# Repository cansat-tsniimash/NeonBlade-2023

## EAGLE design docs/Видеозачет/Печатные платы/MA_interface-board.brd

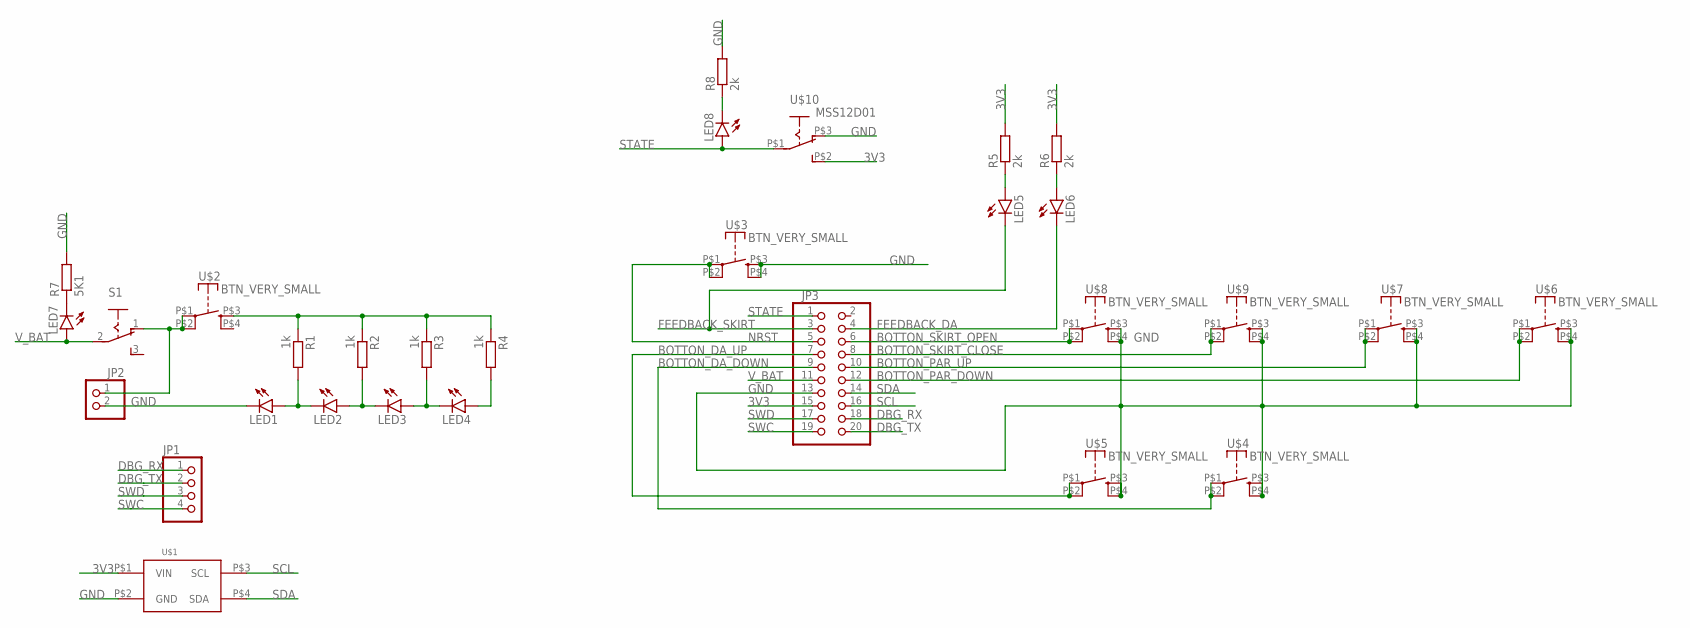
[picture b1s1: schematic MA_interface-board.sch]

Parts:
JP1: PINHD-1X4; 1X04
JP2: PINHD-1X2; 1X02
JP3: PINHD-2X10; 2X10
LED1, LED2, LED3, LED4, LED5, LED6, LED7, LED8: LEDSML0603; SML0603
R1, R2, R3, R4: 1k; R0603
R5, R6, R8: 2k; R0603
R7: 5K1; R0603
S1: UNICS-SWITCH
U$1: BME280BME280-PINS-ONLY; BME280-PINS-ONLY
U$2, U$3, U$4, U$5, U$6, U$7, U$8, U$9: BTN_VERY_SMALL
U$10: MSS12D01

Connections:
3V3: JP3.15, R5.2, R6.2, U$1.P$1 (VIN), U$10.P$2 (S)
BOTTON_DA_DOWN: JP3.9, U$4.P$1, U$4.P$2
BOTTON_DA_UP: JP3.7, U$5.P$1, U$5.P$2
BOTTON_PAR_DOWN: JP3.12, U$6.P$1, U$6.P$2
BOTTON_PAR_UP: JP3.10, U$7.P$1, U$7.P$2
BOTTON_SKIRT_CLOSE: JP3.8, U$9.P$1, U$9.P$2
BOTTON_SKIRT_OPEN: JP3.6, U$8.P$1, U$8.P$2
DBG_RX: JP1.1, JP3.18
DBG_TX: JP1.2, JP3.20
FEEDBACK_DA: JP3.4, LED6.C
FEEDBACK_SKIRT: JP3.3, LED5.C
GND: JP2.2, JP3.13, LED1.C, R7.2, R8.2, U$1.P$2 (GND), U$3.P$3 (S), U$3.P$4 (S), U$4.P$3 (S), U$4.P$4 (S), U$5.P$3 (S), U$5.P$4 (S), U$6.P$3 (S), U$6.P$4 (S), U$7.P$3 (S), U$7.P$4 (S), U$8.P$3 (S), U$8.P$4 (S), U$9.P$3 (S), U$9.P$4 (S), U$10.P$3 (O)
unnamed: LED1.A, LED2.C, R1.2
unnamed: LED2.A, LED3.C, R2.2
unnamed: LED3.A, LED4.C, R3.2
unnamed: LED4.A, R4.2
unnamed: LED7.C, R7.1
unnamed: JP2.1, S1.1 (O), U$2.P$1, U$2.P$2
unnamed: R1.1, R2.1, R3.1, R4.1, U$2.P$3 (S)
unnamed: LED5.A, R5.1
unnamed: LED6.A, R6.1
unnamed: LED8.C, R8.1
NRST: JP3.5, U$3.P$1, U$3.P$2
SCL: JP3.16, U$1.P$3 (SCL)
SDA: JP3.14, U$1.P$4 (SDA)
STATE: JP3.1, LED8.A, U$10.P$1
SWC: JP1.4, JP3.19
SWD: JP1.3, JP3.17
V_BAT: JP3.11, LED7.A, S1.2

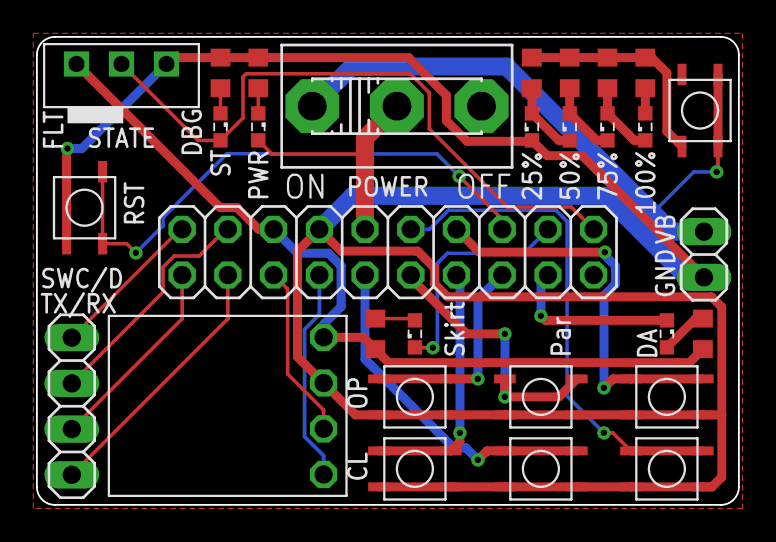
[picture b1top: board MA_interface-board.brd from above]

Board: 2 copper layers, 39.0 x 26.0 mm, 30 parts (0 on the bottom side), 29 nets.

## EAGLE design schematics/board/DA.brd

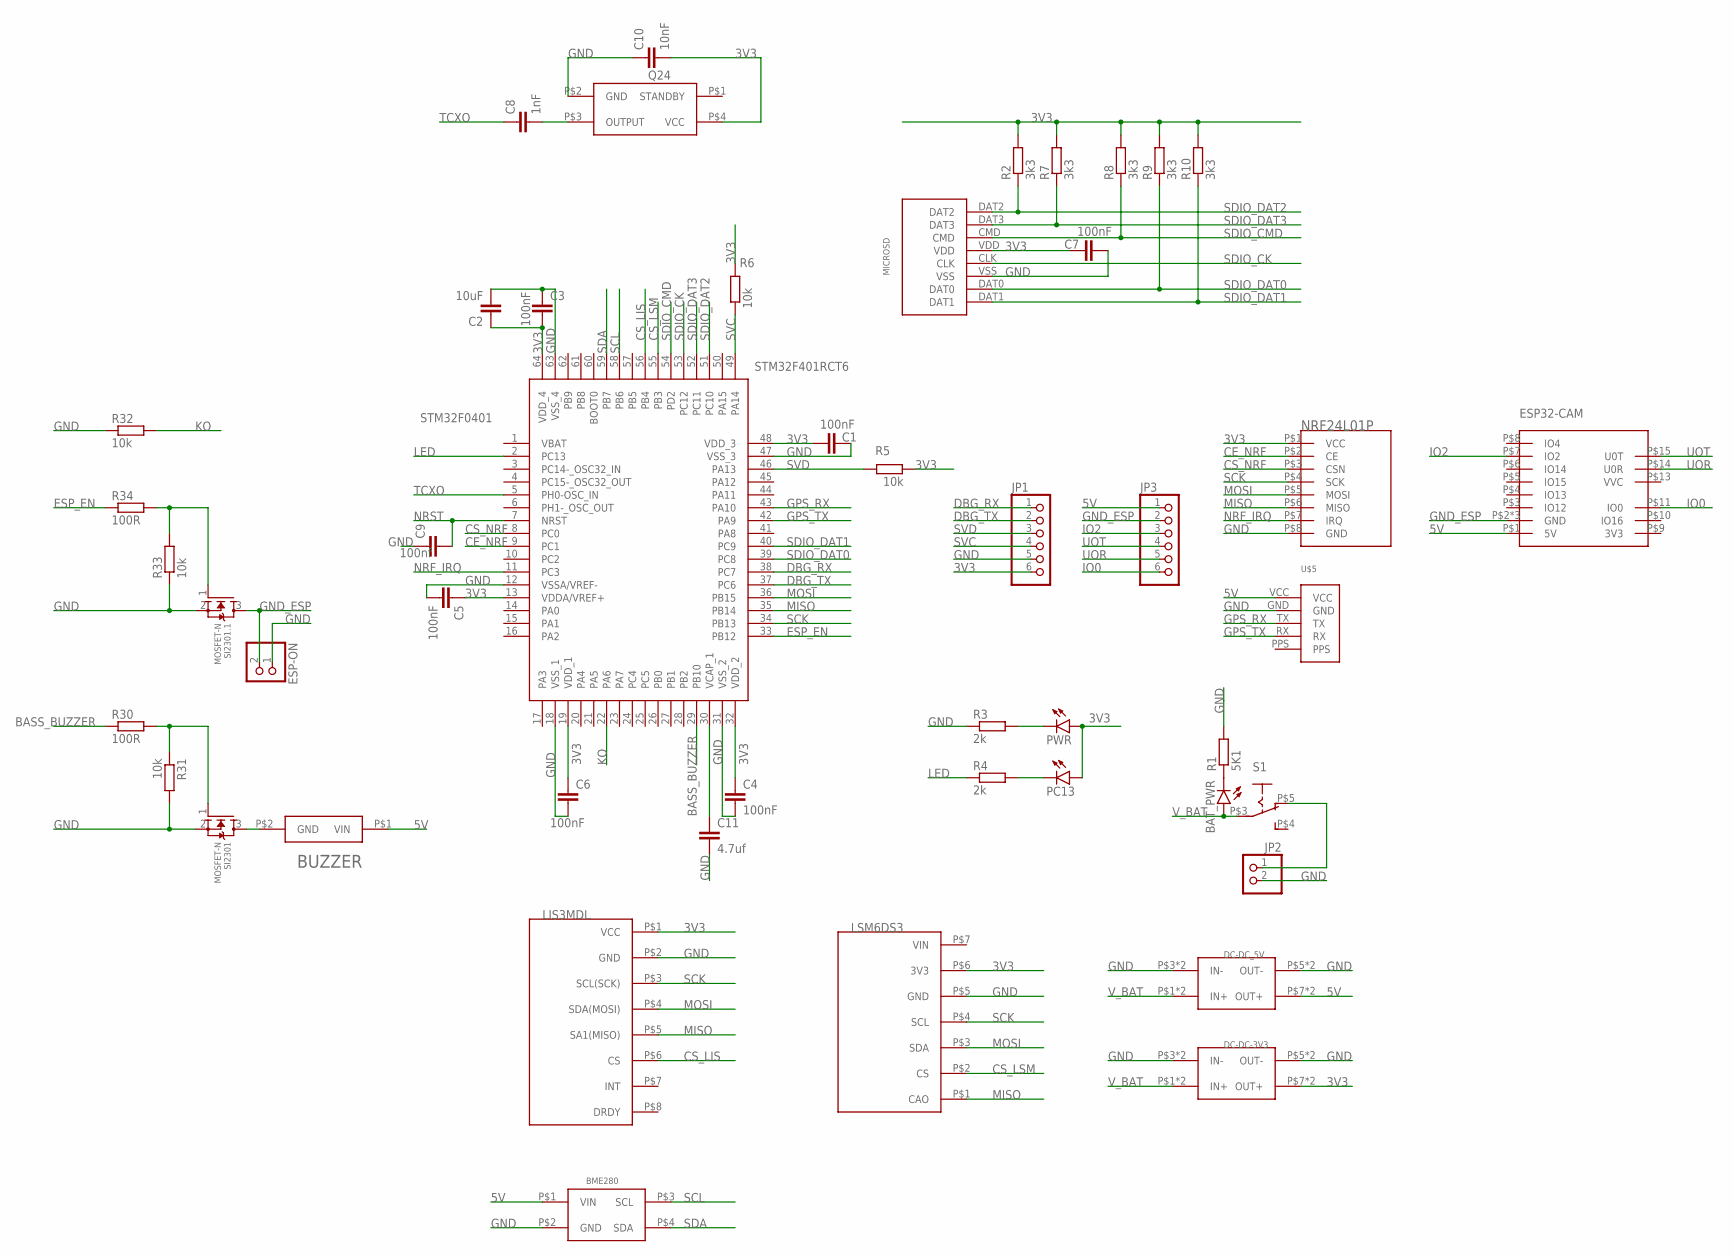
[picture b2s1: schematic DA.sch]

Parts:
BAT_PWR: LEDSML0603; SML0603
BME280: BME280BME280-PINS-ONLY; BME280-PINS-ONLY
BUZZER: BUZZERS8R6; BUZZER-S8R12
C1, C3, C4, C5, C6, C7: 100nF; C0603
C2: 10uF; C1206
C8: 1nF; C0603
C9: 100nf; C0603
C10: 10nF; C0603
C11: 4.7uf; C0603
DC-DC-3V3: MP1584-B
DC-DC_5V: MP1584-B
ESP32-CAM: ESP32-CAM
ESP-ON: PINHD-1X2; 1X02
JP1, JP3: PINHD-1X6; 1X06
JP2: PINHD-1X2; 1X02
LIS3MDL: LIS3MDL-CJMCUбез_отв.; LIS3MDL-CGMSU-NB2023-1
LSM6DS3: LSM6DS3-GY-NB2023Без_отв.; LSM6DS3-GY-NB2023-1
MICROSD: SD
NRF24L01P: NRF24L01_ML01SP4
PC13: LEDCHIPLED_0603; CHIPLED_0603
PWR: LEDCHIPLED_0603; CHIPLED_0603
Q24: Q24
R1: 5K1; R0603
R2, R7, R8, R9, R10: 3k3; R0603
R3, R4: 2k; R0603
R5, R6, R31, R32, R33: 10k; R0603
R30, R34: 100R; R0603
S1: UNICS-SWITCH; SWITCH_SK-12F14
SI2301, SI2301.1: MOSFET-N; SOT23-3
STM32F0401: STM32F401RCT6; QFP50P1200X1200X160-64N
U$5: GPS_NEO7M_W-PPS; GPS_NEO7M_W-PPS_&_ANT

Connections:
3V3: C1.2, C2.1, C3.2, C4.1, C5.1, C6.1, C7.2, C10.2, DC-DC-3V3.P$7 (OUT+), DC-DC-3V3.P$8 (OUT+), JP1.6, LIS3MDL.P$1 (VCC), LSM6DS3.P$6 (3V3), MICROSD.VDD, NRF24L01P.P$1 (VCC), PC13.A, PWR.A, Q24.P$4 (VCC), R2.2, R5.2, R6.2, R7.2, R8.2, R9.2, R10.2, STM32F0401.13 (VDDA/VREF+), STM32F0401.19 (VDD_1), STM32F0401.32 (VDD_2), STM32F0401.48 (VDD_3), STM32F0401.64 (VDD_4)
5V: BME280.P$1 (VIN), BUZZER.P$1 (VIN), DC-DC_5V.P$7 (OUT+), DC-DC_5V.P$8 (OUT+), ESP32-CAM.P$1 (5V), JP3.1, U$5.VCC
BASS_BUZZER: R30.1, STM32F0401.29 (PB10)
CE_NRF: NRF24L01P.P$2 (CE), STM32F0401.9 (PC1)
CS_LIS: LIS3MDL.P$6 (CS), STM32F0401.56 (PB4)
CS_LSM: LSM6DS3.P$2 (CS), STM32F0401.55 (PB3)
CS_NRF: NRF24L01P.P$3 (CSN), STM32F0401.8 (PC0)
DBG_RX: JP1.1, STM32F0401.38 (PC7)
DBG_TX: JP1.2, STM32F0401.37 (PC6)
ESP_EN: R34.1, STM32F0401.33 (PB12)
GND: BME280.P$2 (GND), C1.1, C2.2, C3.1, C4.2, C5.2, C6.2, C7.1, C9.1, C10.1, C11.2, DC-DC-3V3.P$3 (IN-), DC-DC-3V3.P$4 (IN-), DC-DC-3V3.P$5 (OUT-), DC-DC-3V3.P$6 (OUT-), DC-DC_5V.P$3 (IN-), DC-DC_5V.P$4 (IN-), DC-DC_5V.P$5 (OUT-), DC-DC_5V.P$6 (OUT-), ESP-ON.1, JP1.5, JP2.2, LIS3MDL.P$2 (GND), LSM6DS3.P$5 (GND), MICROSD.VSS, NRF24L01P.P$8 (GND), Q24.P$2 (GND), R1.2, R3.1, R31.2, R32.1, R33.1, SI2301.2 (S), SI2301.1.2 (S), STM32F0401.12 (VSSA/VREF-), STM32F0401.18 (VSS_1), STM32F0401.31 (VSS_2), STM32F0401.47 (VSS_3), STM32F0401.63 (VSS_4), U$5.GND
GND_ESP: ESP32-CAM.P$2 (GND), ESP32-CAM.P$12 (GND), ESP32-CAM.P$16 (GND), ESP-ON.2, JP3.2, SI2301.1.3 (D)
GPS_RX: STM32F0401.43 (PA10), U$5.TX
GPS_TX: STM32F0401.42 (PA9), U$5.RX
IO0: ESP32-CAM.P$11 (IO0), JP3.6
IO2: ESP32-CAM.P$7 (IO2), JP3.3
KO: R32.2, STM32F0401.22 (PA6)
LED: R4.1, STM32F0401.2 (PC13)
MISO: LIS3MDL.P$5 (SA1(MISO)), LSM6DS3.P$1 (CAO), NRF24L01P.P$6 (MISO), STM32F0401.35 (PB14)
MOSI: LIS3MDL.P$4 (SDA(MOSI)), LSM6DS3.P$3 (SDA), NRF24L01P.P$5 (MOSI), STM32F0401.36 (PB15)
unnamed: R30.2, R31.1, SI2301.1 (G)
unnamed: R33.2, R34.2, SI2301.1.1 (G)
unnamed: BAT_PWR.C, R1.1
unnamed: JP2.1, S1.P$5 (O)
unnamed: C8.2, Q24.P$3 (OUTPUT)
unnamed: C11.1, STM32F0401.30 (VCAP_1)
unnamed: BUZZER.P$2 (GND), SI2301.3 (D)
unnamed: PWR.C, R3.2
unnamed: PC13.C, R4.2
NRF_IRQ: NRF24L01P.P$7 (IRQ), STM32F0401.11 (PC3)
NRST: C9.2, STM32F0401.7 (NRST)
SCK: LIS3MDL.P$3 (SCL(SCK)), LSM6DS3.P$4 (SCL), NRF24L01P.P$4 (SCK), STM32F0401.34 (PB13)
SCL: BME280.P$3 (SCL), STM32F0401.58 (PB6)
SDA: BME280.P$4 (SDA), STM32F0401.59 (PB7)
SDIO_CK: MICROSD.CLK, STM32F0401.53 (PC12)
SDIO_CMD: MICROSD.CMD, R8.1, STM32F0401.54 (PD2)
SDIO_DAT0: MICROSD.DAT0, R9.1, STM32F0401.39 (PC8)
SDIO_DAT1: MICROSD.DAT1, R10.1, STM32F0401.40 (PC9)
SDIO_DAT2: MICROSD.DAT2, R2.1, STM32F0401.51 (PC10)
SDIO_DAT3: MICROSD.DAT3, R7.1, STM32F0401.52 (PC11)
SVC: JP1.4, R6.1, STM32F0401.49 (PA14)
SVD: JP1.3, R5.1, STM32F0401.46 (PA13)
TCXO: C8.1, STM32F0401.5 (PH0-OSC_IN)
UOR: ESP32-CAM.P$14 (U0R), JP3.5
UOT: ESP32-CAM.P$15 (U0T), JP3.4
V_BAT: BAT_PWR.A, DC-DC-3V3.P$1 (IN+), DC-DC-3V3.P$2 (IN+), DC-DC_5V.P$1 (IN+), DC-DC_5V.P$2 (IN+), S1.P$3

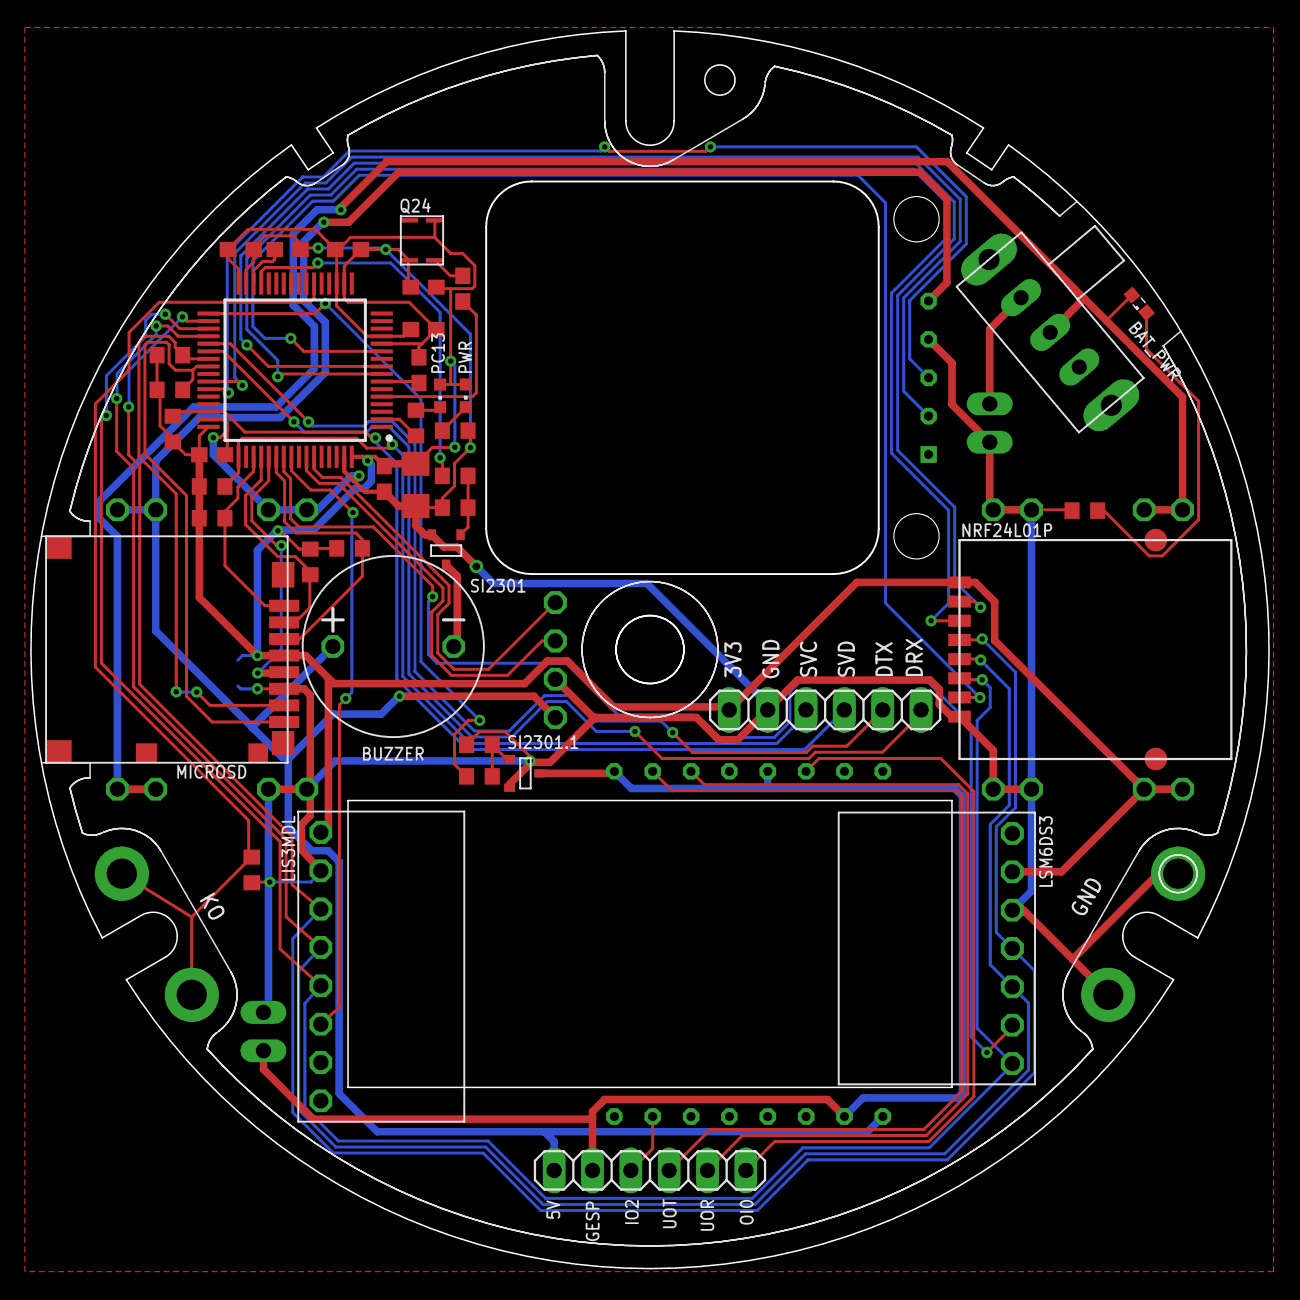
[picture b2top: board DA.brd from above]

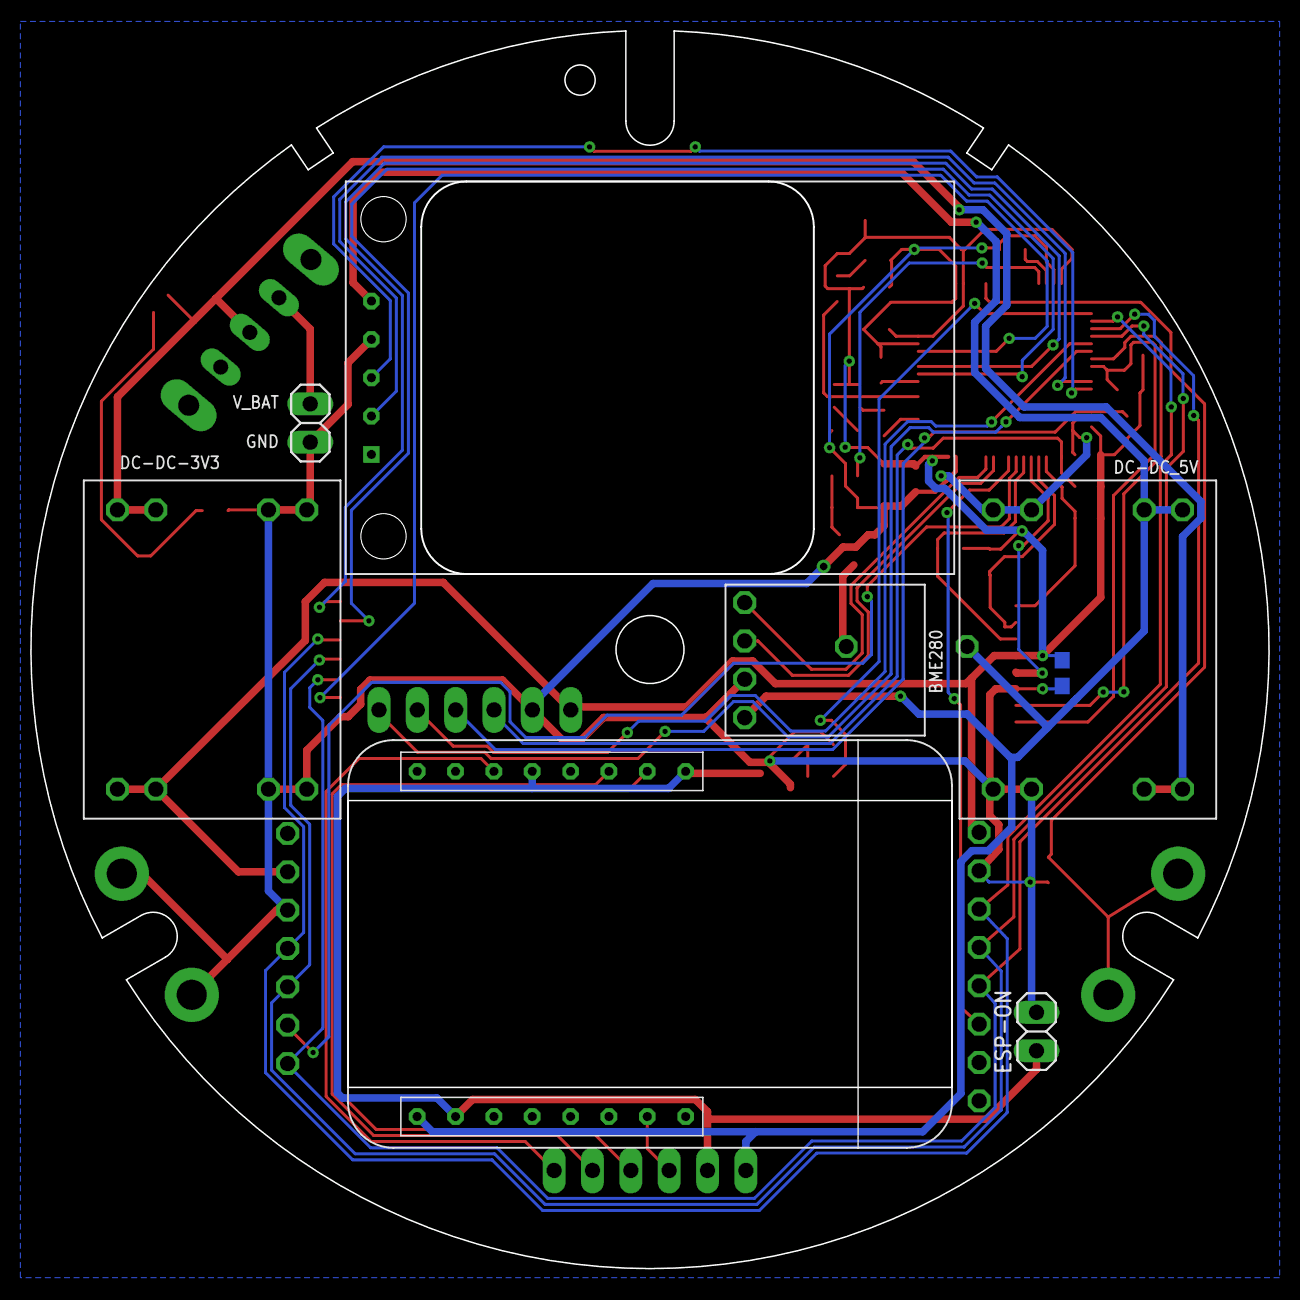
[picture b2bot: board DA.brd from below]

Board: 2 copper layers, 82.0 x 81.9 mm, 48 parts (7 on the bottom side), 46 nets.

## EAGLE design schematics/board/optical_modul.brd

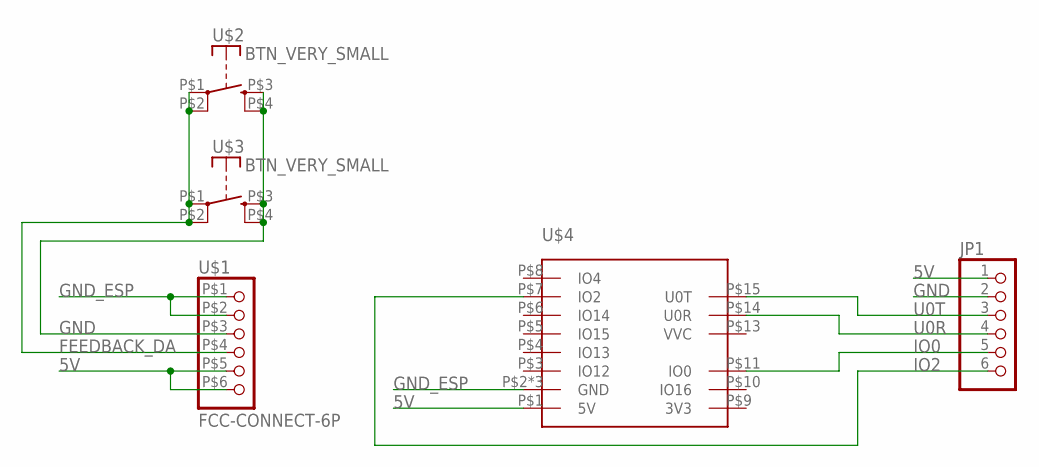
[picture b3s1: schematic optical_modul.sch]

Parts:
JP1: PINHD-1X6; 1X06
U$1: FCC-CONNECT-6P; FFC-CONNECT-6P-SMD
U$2, U$3: BTN_VERY_SMALL
U$4: ESP32-CAM

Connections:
5V: JP1.1, U$1.P$5 (5), U$1.P$6 (6), U$4.P$1 (5V)
FEEDBACK_DA: U$1.P$4 (4), U$2.P$1, U$2.P$2, U$3.P$1, U$3.P$2
GND: JP1.2, U$1.P$3 (3), U$2.P$3 (S), U$2.P$4 (S), U$3.P$3 (S), U$3.P$4 (S)
GND_ESP: U$1.P$1 (1), U$1.P$2 (2), U$4.P$2 (GND), U$4.P$12 (GND), U$4.P$16 (GND)
IO0: JP1.5, U$4.P$11 (IO0)
IO2: JP1.6, U$4.P$7 (IO2)
U0R: JP1.4, U$4.P$14 (U0R)
U0T: JP1.3, U$4.P$15 (U0T)

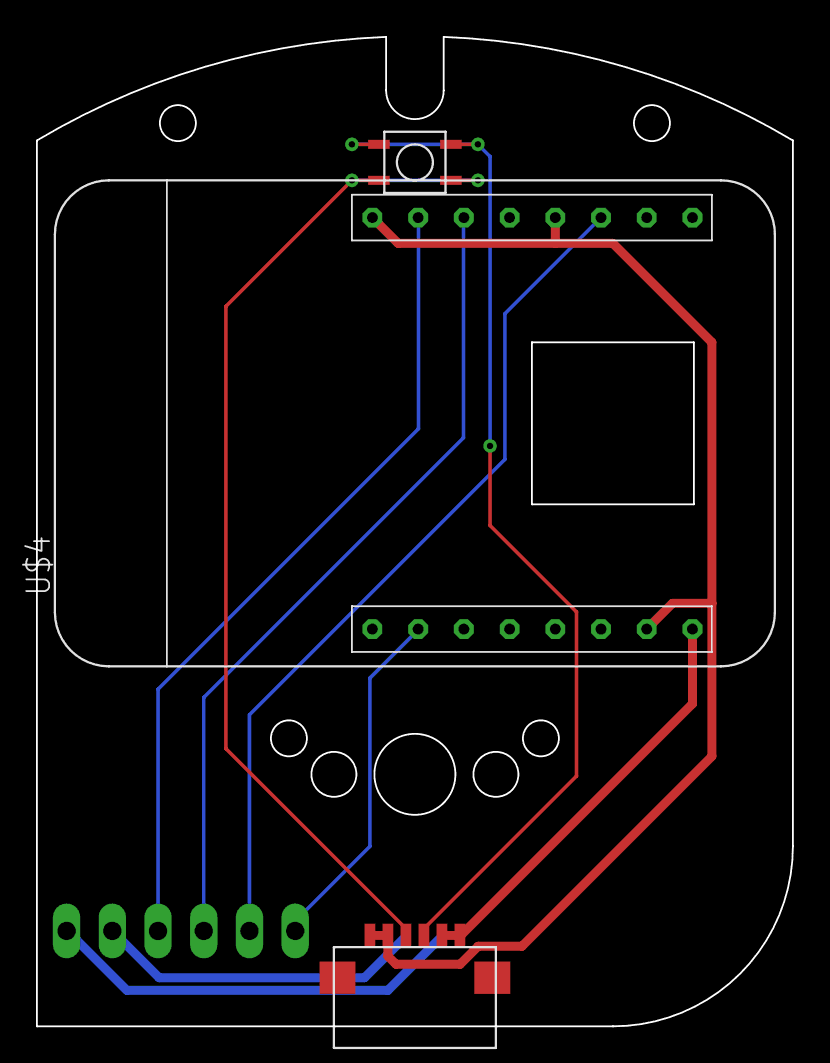
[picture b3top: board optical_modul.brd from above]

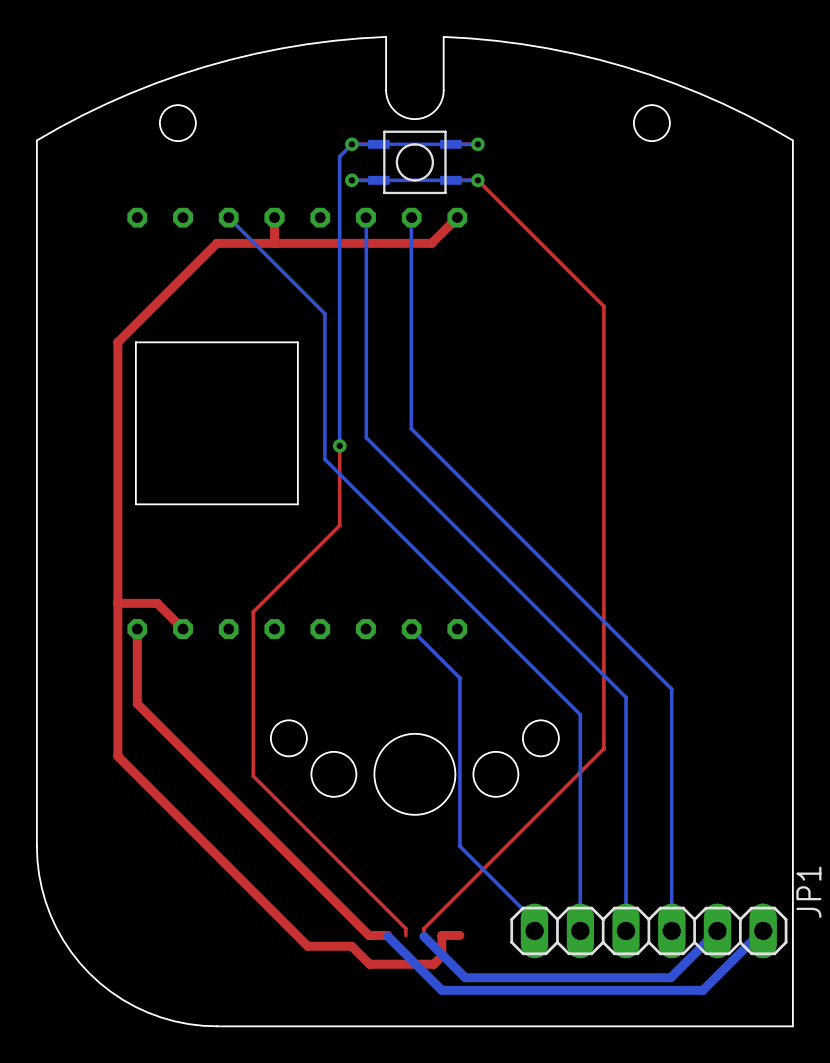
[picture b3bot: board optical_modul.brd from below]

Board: 2 copper layers, 42.0 x 55.0 mm, 5 parts (2 on the bottom side), 8 nets.

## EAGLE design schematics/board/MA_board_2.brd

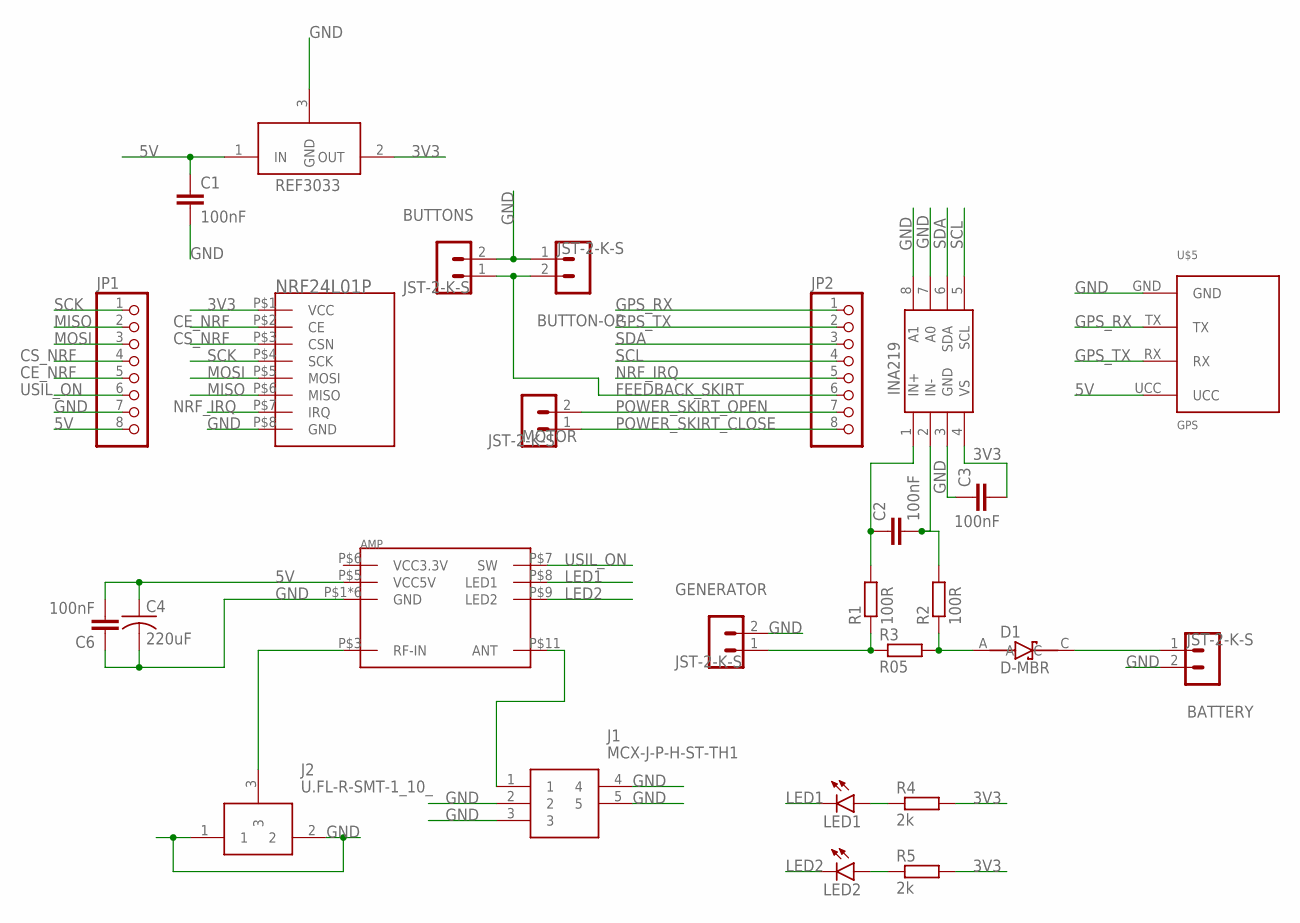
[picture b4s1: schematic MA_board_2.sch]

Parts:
AMP: XQ-02A
BATTERY: JST-2-K-S; B2B-PH-K-S
BUTTON-OP: JST-2-K-S; B2B-PH-K-S
BUTTONS: JST-2-K-S; B2B-PH-K-S
C1, C2, C3, C6: 100nF; C0603
C4: 220uF; ECAP220-CMD
D1: D-MBR; SOD123
GENERATOR: JST-2-K-S; B2B-PH-K-S
INA219: INA219AID; SOT23-8
J1: MCX-J-P-H-ST-TH1; MCXJPHSTTH1
J2: U.FL-R-SMT-1_10_; U.FL-R-SMT-1(10)
JP1, JP2: PINHD-1X8-SHORT-PAD; 1X08
LED1, LED2: LEDSML0603; SML0603
MOTOR: JST-2-K-S; B2B-PH-K-S
NRF24L01P: NRF24L01_ML01SP4
R1, R2: 100R; R0603
R3: R05; R2512
R4, R5: 2k; R0603
REF3033: REF3033; SOT23-3
U$5: GPS

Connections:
3V3: C3.2, INA219.4 (VS), NRF24L01P.P$1 (VCC), R4.2, R5.2, REF3033.2 (OUT)
5V: AMP.P$5 (VCC5V), C1.1, C4.P$1 (1), C6.2, JP1.8, REF3033.1 (IN), U$5.UCC
CE_NRF: JP1.5, NRF24L01P.P$2 (CE)
CS_NRF: JP1.4, NRF24L01P.P$3 (CSN)
FEEDBACK_SKIRT: BUTTON-OP.2, BUTTONS.1, JP2.6
GND: AMP.P$1 (GND), AMP.P$2 (GND), AMP.P$4 (GND), AMP.P$10 (GND), AMP.P$12 (GND), AMP.P$13 (GND), BATTERY.2, BUTTON-OP.1, BUTTONS.2, C1.2, C3.1, C4.P$2 (2), C6.1, GENERATOR.2, INA219.3 (GND), INA219.7 (A0), INA219.8 (A1), J1.2, J1.3, J1.4, J1.5, J2.1, J2.2, JP1.7, NRF24L01P.P$8 (GND), REF3033.3 (GND), U$5.GND
GPS_RX: JP2.1, U$5.TX
GPS_TX: JP2.2, U$5.RX
LED1: AMP.P$8 (LED1), LED1.C
LED2: AMP.P$9 (LED2), LED2.C
MISO: JP1.2, NRF24L01P.P$6 (MISO)
MOSI: JP1.3, NRF24L01P.P$5 (MOSI)
unnamed: C2.1, INA219.1 (IN+), R1.2
unnamed: AMP.P$3 (RF-IN), J2.3
unnamed: AMP.P$11 (ANT), J1.1
unnamed: GENERATOR.1, R1.1, R3.1
unnamed: C2.2, INA219.2 (IN-), R2.2
unnamed: BATTERY.1, D1.C
unnamed: LED1.A, R4.1
unnamed: D1.A, R2.1, R3.2
unnamed: LED2.A, R5.1
NRF_IRQ: JP2.5, NRF24L01P.P$7 (IRQ)
POWER_SKIRT_CLOSE: JP2.8, MOTOR.1
POWER_SKIRT_OPEN: JP2.7, MOTOR.2
SCK: JP1.1, NRF24L01P.P$4 (SCK)
SCL: INA219.5 (SCL), JP2.4
SDA: INA219.6 (SDA), JP2.3
USIL_ON: AMP.P$7 (SW), JP1.6

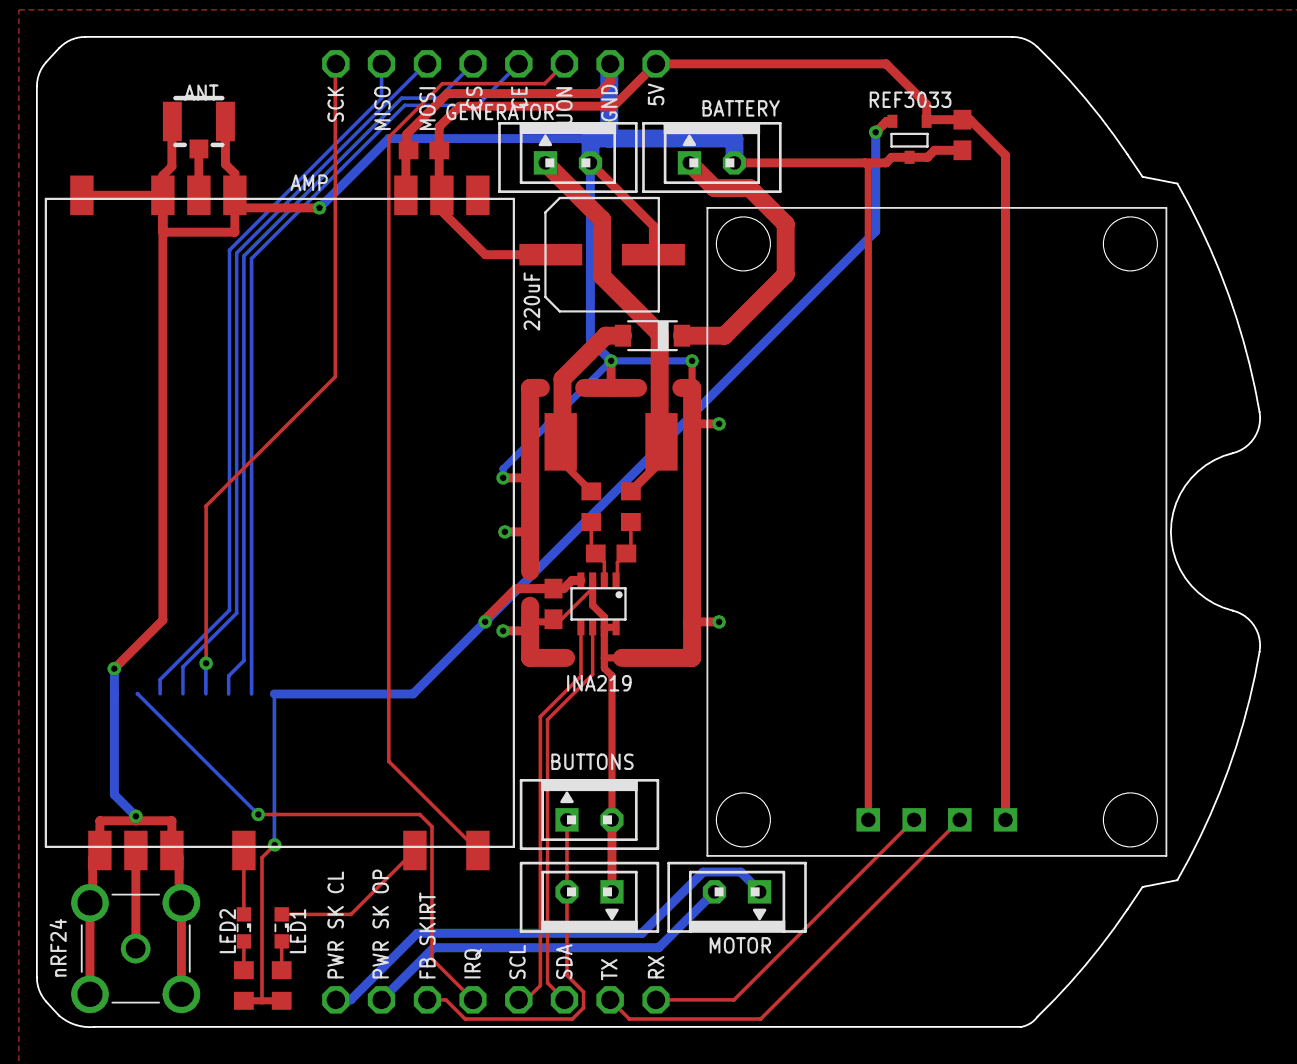
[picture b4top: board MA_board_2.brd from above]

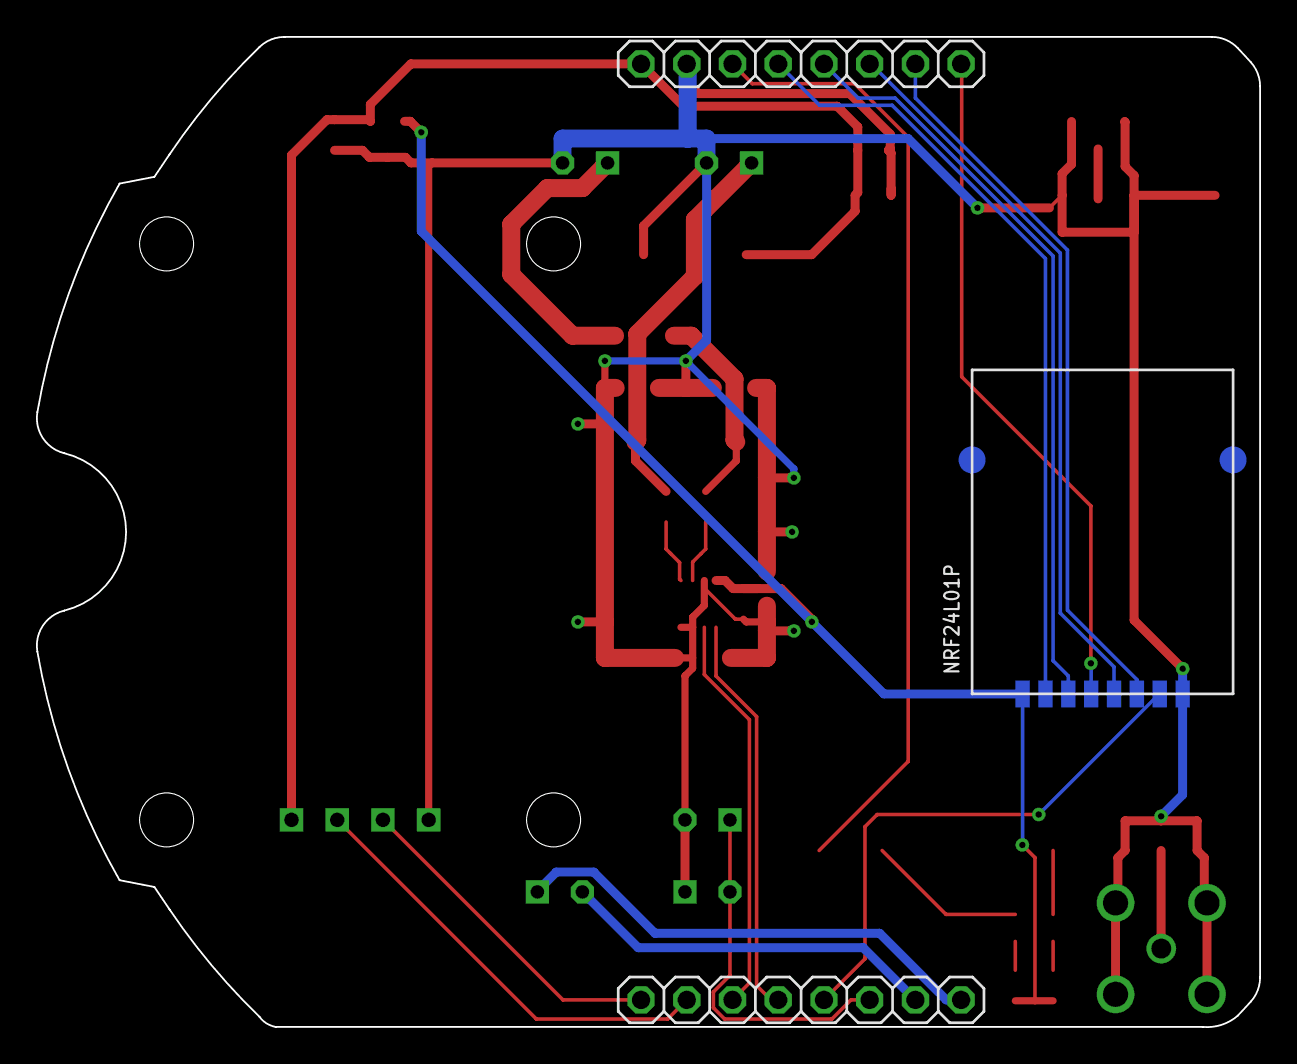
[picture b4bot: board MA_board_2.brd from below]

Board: 2 copper layers, 68.0 x 55.0 mm, 27 parts (3 on the bottom side), 28 nets.

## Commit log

2022-10-15 Начало проекта!
2022-10-15 Закинул скрипт для моделей Creo
2022-10-15 продвинул компоновку ДА
2022-11-26 Собрал классный аппарат, назначил его массу
2022-11-26 Я сделал классный дочерний аппарат
2022-11-26 Добавили классные поддержки, увеличили отверстия под гайки
2022-11-29 Назначил массу дочернему аппарату. Общая массса зонда составила 560 грамм
2022-11-29 В догонку
2022-12-03 Вернули в модель дочерние аппараты
2022-12-21 переработаная бабара-бабина
2022-12-21 сделали анимацию для юбок
2022-12-23 видосик с отделением ДА
2022-12-23 Добавил шкив
2023-01-27 сделали 5д модельки для печати
2023-01-28 Доработка проектной модели для зимней сессии
2023-01-28 делаем отверстия под парашют дочек
2023-01-28 Добавили документы на зимнюю сессию
2023-02-08 Создан габаритный чертеж
2023-02-08 Добавлены направляющие для крышки паращютного отсека
2023-02-08 я сделял платы
2023-02-10 Добавил библиотеки для разработки печатных плат
2023-02-13 Перенес DXF файлы в соответствующую папку
2023-02-13 Проверил схему платы: добавил схемы управления ESP32, контакта отделения (КО), исправил ошибку с подключением транзистора для управления двигателя. Сделал примерку футпринтов на плату
2023-02-13 Дополнена компоновка плат МА в 3D модели
2023-02-17 Добавлен проект в Eagle
2023-02-18 новая версия первой платы нижнего модуля
2023-02-18 Создан проект второй платы МА
2023-02-18 начали делать интерфейсную плату
2023-02-18 немного продвинул работу над платой (Прмгите)
2023-02-18 я весь день делал плату с гпской
2023-02-19 Проверил платы. Исправил некоторые ошибки
2023-02-19 Добавил отверстия для крепления к нижнему модулю. Жаль, вспомнили про них, когда уже напечатали
2023-02-19 Commitfix
2023-02-23 Я Тимофей, и я сделал плату. Гыы...
2023-02-23 Я Данижок, и я тоже сделал плату. А куратор за всех коммитит и выключает компьютеры((
2023-02-24 залили два проекта ДА и МА, которые общаются без акков
2023-02-24 ну короче сделал плату оптического модуля
2023-03-01 МА передает быстро, а ДА отправляет ACK редко(
2023-03-04 Делаем уборку
2023-03-04 Убираемся дальше
2023-03-04 МА получает пакеты от ДА вместе с ACK. Ура!
2023-03-15 Ина работает исправно!
2023-03-15 Сам либцниимаш
2023-03-17 отдельный проект для сд. ножек в основном не хватает
2023-03-24 Сделана плата дочерних аппаратов
2023-03-24 Доработана 3D модель по результатам разводки платы ДА
2023-03-24 Создана платка с кнопкой
2023-03-24 Обновлены DXF файлы для плат
2023-03-24 Все платы проверены и вроеде бы как готовы к изготовлению!
2023-03-25 доработал верхний модуль и другую часть конструкции
2023-03-26 Еще раз проверил все платы и подготовил для производства в Резоните
2023-03-29 Переписал драйвер BME280 студлиги под наш проект. Теперь надо отлаживать
2023-04-05 Доработаны модели верхнего модуля. Подготовлены STLs
2023-04-14 Доработана модель корпуса ДА
2023-04-14 причина ненависти к пружинам
2023-04-15 исправляем ошибки в моделях
2023-04-15 кнопку сохранить придумали до... (исправил крышку дочерки)
2023-04-15 обрезал лил узи
2023-04-15 Зачатки ПЗ
2023-04-21 ПЗ обновлена
2023-05-01 Глобальный ребрендинг 3D моделей
2023-05-01 Создали спецификации атмосферного зонда
2023-05-01 Модели для печати
2023-05-01 Файлы печатных плат для видеозачета
2023-05-01 Черноглазов Данила написал код для ESP32-CAM
2023-05-01 Воронов Даниил написал код для обработчика наземки
2023-05-13 новая версия юбки
2023-05-17 Комплекты плат, которые были отправлены на производство (кроме платы ДА)
2023-05-17 Скрыл поддержки у детали
2023-05-17 Добавлены материалы к видеозачету кроме видео
2023-05-24 Модернизировал верхний модуль
2023-05-26 Учёл недочёты в обтекателе
2023-05-26 Добавил отверстия для строп ДА

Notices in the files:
src/board/bme_proj/Core/Src/stm32f4xx_hal_msp.c:
Copyright (c) 2022 STMicroelectronics.
All rights reserved.
This software is licensed under terms that can be found in the LICENSE file
